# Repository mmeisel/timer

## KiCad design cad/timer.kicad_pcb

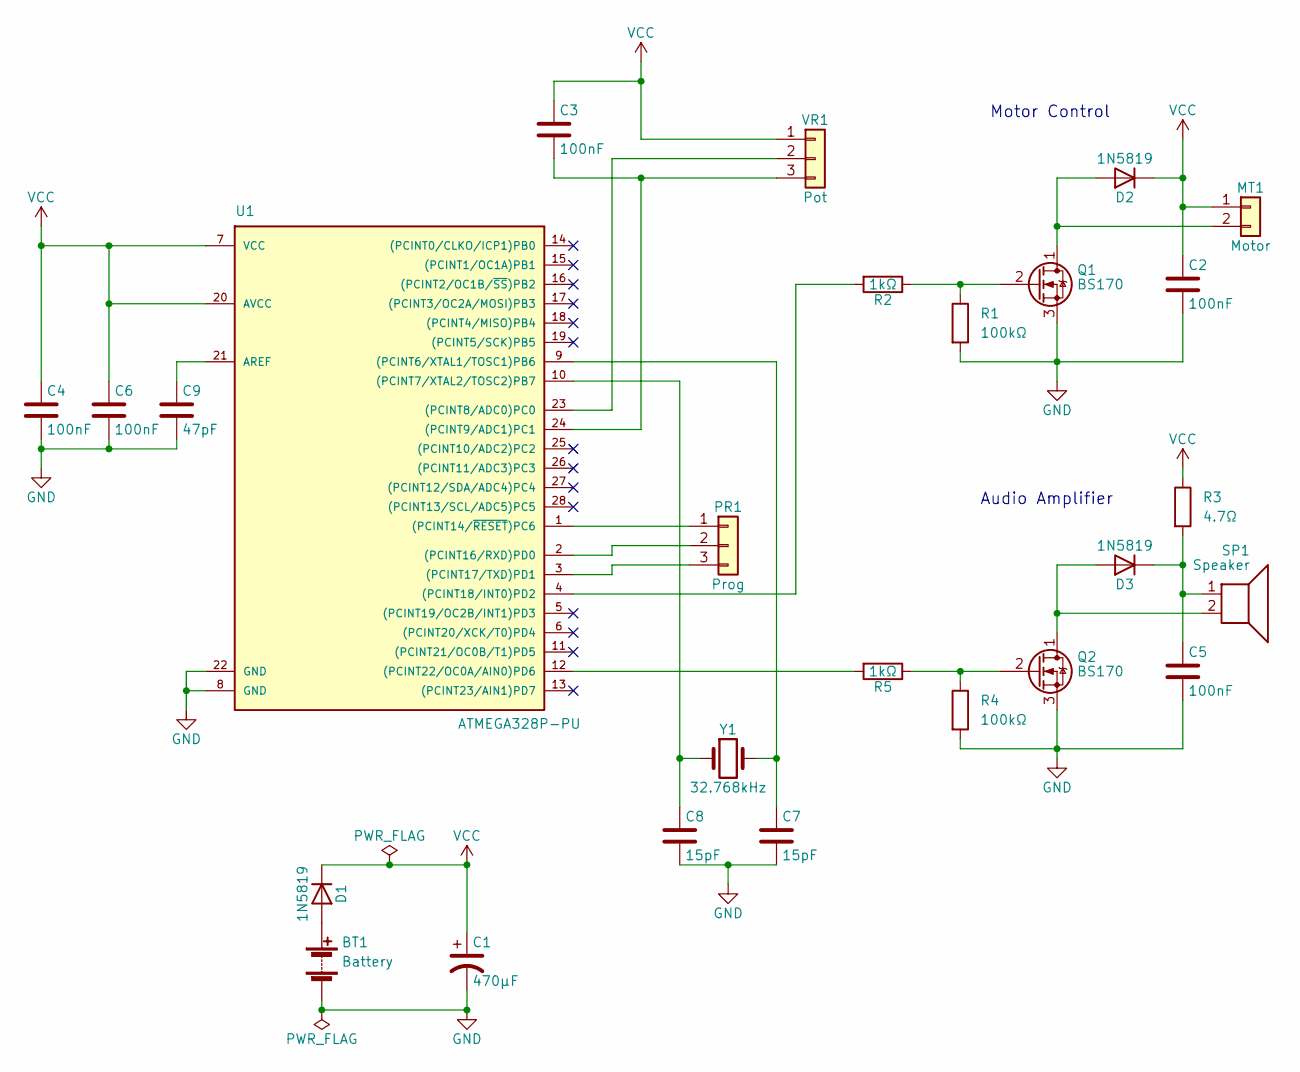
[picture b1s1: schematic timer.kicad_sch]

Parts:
BT1: Battery; PinHeader_1x02_P2.54mm_Vertical
C1: 470µF; CP_Radial_D10.0mm_P5.00mm
C2, C3, C4, C5, C6: 100nF; C_Disc_D5.0mm_W2.5mm_P5.00mm
C7, C8: 15pF; C_Disc_D5.0mm_W2.5mm_P2.50mm
C9: 47pF; C_Disc_D5.0mm_W2.5mm_P2.50mm
D1, D2, D3: 1N5819; D_DO-41_SOD81_P2.54mm_Vertical_KathodeUp
MT1: Motor; PinHeader_1x02_P2.54mm_Vertical
PR1: Prog; PinHeader_1x03_P2.54mm_Vertical
Q1, Q2: BS170; TO-92_Inline_Wide
R1, R4: 100kΩ; R_Axial_DIN0207_L6.3mm_D2.5mm_P2.54mm_Vertical
R2, R5: 1kΩ; R_Axial_DIN0207_L6.3mm_D2.5mm_P2.54mm_Vertical
R3: 4.7Ω; R_Axial_DIN0207_L6.3mm_D2.5mm_P2.54mm_Vertical
SP1: Speaker; PinHeader_1x02_P2.54mm_Vertical
U1: ATMEGA328P-PU; DIP-28_W7.62mm_Socket
VR1: Pot; PinHeader_1x03_P2.54mm_Vertical
Y1: 32.768kHz; Crystal_C38-LF_D3.0mm_L8.0mm_Vertical

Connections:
GND: BT1.2 (-), C1.2, C2.2, C4.2, C5.2, C6.2, C7.2, C8.2, C9.2, Q1.3 (S), Q2.3 (S), R1.2, R4.2, U1.8 (GND), U1.22 (GND)
unnamed: BT1.1 (+), D1.2 (A)
unnamed: C3.2, U1.24 ((PCINT9/ADC1)PC1), VR1.3
unnamed: C5.1, D3.1 (K), R3.2, SP1.1
unnamed: C7.1, U1.9 ((PCINT6/XTAL1/TOSC1)PB6), Y1.2
unnamed: C8.1, U1.10 ((PCINT7/XTAL2/TOSC2)PB7), Y1.1
unnamed: C9.1, U1.21 (AREF)
unnamed: D2.2 (A), MT1.2, Q1.1 (D)
unnamed: D3.2 (A), Q2.1 (D), SP1.2
unnamed: PR1.1, U1.1 ((PCINT14/~RESET)PC6)
unnamed: PR1.2, U1.2 ((PCINT16/RXD)PD0)
unnamed: PR1.3, U1.3 ((PCINT17/TXD)PD1)
unnamed: Q1.2 (G), R1.1, R2.1
unnamed: Q2.2 (G), R4.1, R5.1
unnamed: R2.2, U1.4 ((PCINT18/INT0)PD2)
unnamed: R5.2, U1.12 ((PCINT22/OC0A/AIN0)PD6)
unnamed: U1.23 ((PCINT8/ADC0)PC0), VR1.2
VCC: C1.1, C2.1, C3.1, C4.1, C6.1, D1.1 (K), D2.1 (K), MT1.1, R3.1, U1.7 (VCC), U1.20 (AVCC), VR1.1

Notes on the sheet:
Audio Amplifier
Motor Control

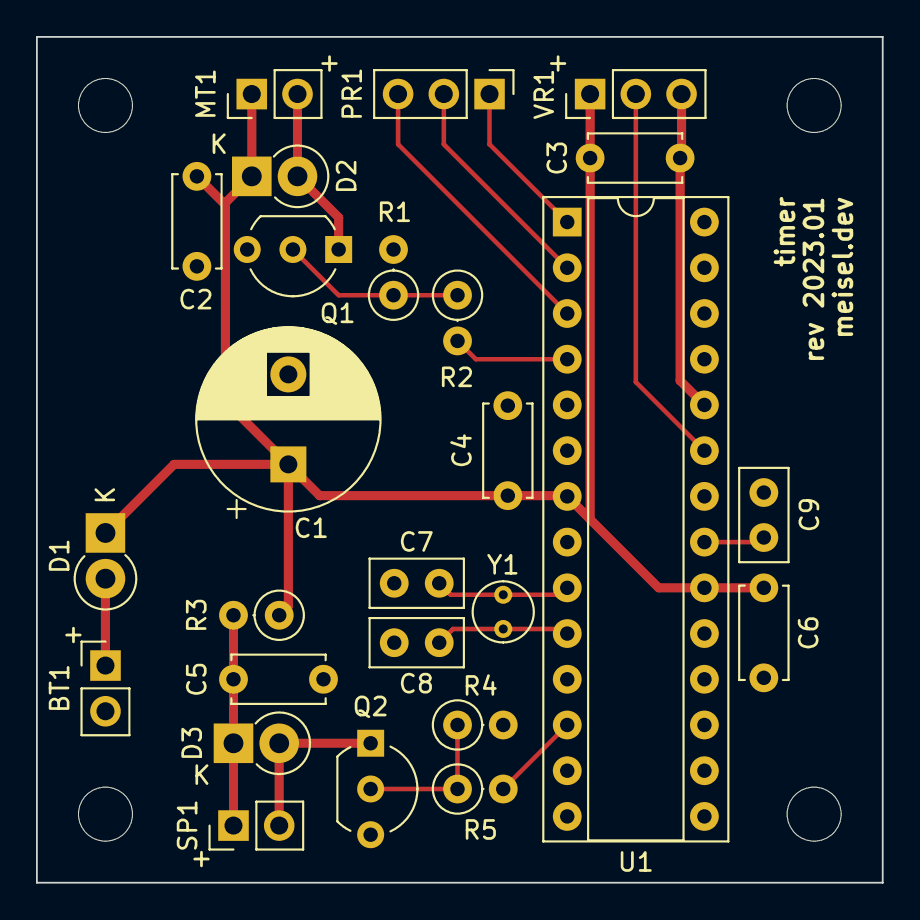
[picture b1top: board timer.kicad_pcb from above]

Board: 2 copper layers, 47.0 x 47.0 mm, 30 parts (0 on the bottom side), 18 nets.

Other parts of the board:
H1, H2, H3, H4: MountingHole_3mm

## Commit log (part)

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2017-07-17 First attempt
    - Using PID to set slider position (untested)
    - Working feedback mechanism with linear scale
2017-07-18 Mostly failed attempt to work with H-Bridge
2017-07-18 Not working version with PID
2017-07-18 Mostly working 30-second linear version
2017-07-19 Reliability and efficiency improvements
2017-07-19 Use binary search in stopBefore
2017-07-19 Tweak some comments
2017-07-19 Fix detentes and improve change detection
2017-07-20 New detentes (non-linear scale)
2017-08-06 Add interrupt for external slide detection circuit
    This doesn't actually do much yet since the microprocessor only sleeps
    for at most 1 ms until the next interrupt for millis(), and it's using
    the highest power sleep mode (idle).
    This will actually start to be useful when using a crystal for the clock
    instead of the Arduino library's (interrupt-based) millis().
2017-08-06 Add notes to version control
2017-08-06 Simpler interrupt handling
2017-08-06 Ignore .DS_Store files
2017-08-06 Initial attempt at interrupt-based timing
2017-08-06 Some code cleanup
2017-08-07 Mostly working low power version!
2017-08-07 Better serial output for debugging
2017-08-08 Some important tweaks for correct operation
2017-08-08 Safer handling of secondsRemaining_
2017-08-08 Don't wake up at all in the OFF position
2017-08-08 TODOs and comments
2017-08-08 Try getting rid of DIR_STOP, doesn't seem to do much
2017-08-08 Use fast stop for longer to see if that stops chatter
2017-08-09 Some notes
2017-08-10 First attempt at new scheme
2017-08-11 Big rewrite
    - Much simpler and more efficient loop() function
    - Sleep a lot more
    - No more detentes for now :(
    - Code cleanup
    - Generate stops of equal size
    - More details in notes.txt
2017-08-14 Fix timing issues by waiting for crystal to stabilize
2017-08-14 Better Timer2 register handling
2017-08-14 Improvements and bug fixes
    - Generate stops on startup instead of on demand
    - Better debug messages
    - Fix tick bug
    - Don't allow the motor to be interrupted
2017-08-24 Some cleanup, tweaks, and notes
    Including:
    - Remove redundant call to updateBell()
    - Better name for power on/off interrupt pin
2017-08-28 Wait for crystal to stabilize by comparing with millis()
2017-09-01 PCM: Use Timer0 instead of Timer2
2017-09-01 Store stops in flash
2017-09-01 Prep for audio generation
    - Add the PCM library from https://github.com/damellis/PCM directly in
    the project (it will need some modifications)
    - Change output pins for compatibility with PCM
    - Some notes on the subject
2017-09-04 Rename stopwatch to clock
2017-09-04 Add source audio file and edited version
2017-09-04 First attempt at complete PCM-based bell
2017-09-14 PCM: More reliable and faster isPlaying() check
2017-09-14 Initialize speaker pin to low
    Otherwise, it wastes power.
2017-09-14 Less lenient position change detection
2017-09-14 Some TODOs
2017-09-14 Fixes for sound generation
    - Don't do anything else while a sound is playing
    - Wait until the motor is done moving the slider into position before
    trying to generate audio
2017-09-15 Remove unnecessary call to updateMotor() on setup()
    We just set the position so there can never be anything to do at
    this point.
2017-09-15 Notes on Class B amplifier circuit
2017-09-15 Remove use of millis() in debug output
    This is already pretty useless and will soon be disabled.
2017-09-15 PCM: Just disable Timer0 instead of restoring it
    Partially reverts 548f2e9945915deeff77d4df83d5430c6061481a
2017-09-15 Fix stopwatch overflow bug
    The subtraction needs to be cast to a signed integer with the same
    number of bits, or the trick doesn't work.
2017-09-15 Use Timer0 directly for stabilization
    This is more accurate than using millis().
2017-09-15 Expose current clock time
2017-09-15 Improve adc reliability
    - Don't try to start two conversions at once
    - Use idle instead of ADC noise reduction low-power mode to avoid
    interfering with Timer2
2017-09-15 Alternative bell sound
    (But I don't like it as much.)
2017-09-15 Play the bell a little less frequently
2017-09-15 Add a TODO
2017-09-15 Switch motor driver on/off with transistor
2017-09-16 Don't set OCR0A initially
    This seems to do nothing other than cause an audible pop.
2017-09-18 bell2 fixup
2017-09-18 Add schematic and unfinished PCB
2017-09-20 Through-hole parts are on front AND back!
2017-09-20 Actual stops for production
2017-09-20 Larger off stop
    No need for zero to be bigger than the other stops, better to have a
    little extra space for the off position. The soft power switch will need
    to have its resistor adjusted accordingly.
2017-09-20 CAD changes for off stop size change
    The soft power switch needs a 68k instead of a 47k resistor now.
2017-10-17 Fix outdated motor-related comment, add note
2017-10-18 Front panel in Front Panel Designer format
    This is the software from Front Panel Express.
2017-10-18 Exported front panel in DXF format
2017-11-08 PCB: Q2 and Q3 labels were switched!
2017-11-30 Fewer stops (39 instead of 60)
2017-11-30 Basic version of 3D-modeled front panel
    Using OpenSCAD
2017-11-30 Clean up front panel slightly
2017-11-30 SCAD code cleanup (fewer braces)
2017-11-30 Front panel: added detentes
2017-11-30 Front panel: fancier off markings
    The same halftone dots as in the Front Panel Designer version
2017-11-30 Front panel: Alternate OFF markings
    With the "OFF" label
2017-11-30 Front panel: Make panel depth adjustable
2017-11-30 Front panel: Deeper engravings
2017-12-02 New 2D version of front panel
    This one is for laser cutting
2017-12-05 2D front panel: More overlap with knob
2017-12-05 Stop at the middle of the stop, not the beginning
2017-12-05 SIGNIFICANT_POSITION_CHANGE is no longer needed
    Using the middle of the stop as the target makes a false detection of
    movement much less likely, so this shouldn't be necessary.
2017-12-05 Front panel: Add SVG for Ponoko
    This had to be customized by hand to meet their design guidelines.
2017-12-07 Front panel: Spread OFF marks to match longer lines
2017-12-10 Updated front panel SVG with recent changes
2017-12-10 Further progress on enclosure for 3D printing
    However, I'm giving up on this approach in favor of laser cutting.
2017-12-12 Start of 2D enclosure for laser cutting
    Still very much WIP. First version of top and back panels.
2017-12-14 More progress on new enclosure
    Still to do:
    - Fix kerf issues
    - Add front panel
    - Add interior panel
    - Add something to mount the battery
2017-12-14 Fixed some kerf issues with 2D enclosure
2017-12-14 Added all panels, still some TODOs
2017-12-15 Fit both batteries and PCB on bottom
2017-12-17 Add screw holes to front panel
2017-12-17 Add correct measurements for slider hole
2017-12-17 Line all parts up
    Two sets will fit on one Ponoko P2 panel this way!
2017-12-17 SVG files for Ponoko laser cut order
    Sent to Ponoko for first run
2017-12-21 Add missing $fn for some screw holes
2017-12-22 Tweak hinge hole position so back panel is flush
2017-12-27 Front panel: Remove corner screw holes
    No need for the holes, I can just glue it
2017-12-27 Front panel: Fix inaccuracy due to slider properties
    According to the datasheet, the slider potentiometer output voltage
    doesn't change for the first or last 2 (+- 1) mm of travel. So spead the
    markings across 96mm instead of 100mm.
2017-12-27 Front panel: More visible off markings
2017-12-27 Front panel: Some tweaks for next run
    - I'm giving up on the tactile feedback for now, so reduce the overlap
    between the knob and the lines
    - Make the lines thinner (they'll just be engraved now)
    - Shrink the width of the slider opening so it stops when it hits the
    plastic instead of at its ultimate limit
2017-12-27 Front panel: New files for next Ponoko order
2017-12-30 More reliable motor controller switch
    The previous resistor/transistor combo wasn't reliable
2017-12-30 Reposition the slider to the center of the stop
    After someone sets the stop manually, move the slider to the center of
    the stop. This serves two purposes:
    - It prevents the timer from getting stuck between two stops when
    positioned at a stop boundary
    - It gives the user some feedback as to which stop was selected
2018-01-07 Remove unused motor function
2018-01-07 Updated schematic and PCB design
    - Increased hole size to 3mm
    - Removed motor controller on/off switch (Q1 and R3)
    - Swap transistor footprint for one that's easier to solder
    - Reroute with FreeRoutingNew
2018-01-10 Refactor for reverse-only motor control
    The L293D has too big a voltage drop to run the already undervolted
    motor on the slider. It both drops Vcc and raises ground due to the
    transistors in the H-bridge.
2018-01-11 Remove extraneous setting of ouptut mode on PCM pin
2018-01-11 Reduce clicks when bell sound starts
    No more clicks! Just needed to ramp up from zero.
2018-01-12 Schematic for updated design
    - Now using MOSFETs for both motor and audio switching
    - Added a bunch of bypass/decoupling capacitors
2018-01-12 New PCB design to match new schematic
    - Isolated power networks with decoupling capacitors
    - Top layer is ground, bottom layer is VCC (this seems to be the
    convention)
    - Hopefully better placement of ports for external devices
2018-01-16 Enclosure: Add some wiggle room for door
2018-01-18 Just some thoughts
2018-01-20 One more note
2018-01-20 New ringing behavior
    - The timer will now only ring a set number of times, then turn itself
    off. This way it won't just keep ringing until it drains the battery
    if it's left ringing unattended.
    - Allow the delay to be variable between rings by providing an array of
    delay intervals.
2018-02-09 Less aggressive bell repetition
2018-02-09 Some notes on battery holders and enclosure
2018-03-28 Add note about "click" branch
2018-03-28 New battery holder
2018-03-28 Fix tilt angle, bottom depth, and clean up code
2018-03-28 Rearrange parts to fit better in ponoko template
2018-03-28 I only need one of these!
2018-03-28 Avoid rounded edges when using offset()
2018-03-28 Add some padding to battery rail cutouts
    For some reason the rendering of these was imprecise.
2018-03-28 Update enclosure SVG files
    Note that the battery crossbar was manually combined with the slider
    cutout using inkscape.
2018-08-21 Enclosure tweaks
    - Remove battery crossbar
    - Slightly more room for battery holder
    - Move PCB mount a bit closer to the rear door
2021-10-12 Prevent warning on newer OpenSCAD
2021-10-15 Add licenses
2021-10-15 First attempt at click sound
2021-10-22 Changes from new kicad version
2022-01-05 Fix some comments
2022-10-10 Remove unused parameter
2022-10-10 Naming tweak for MiniCore compatibility
2022-10-10 Better config/debug system
    No functional changes
2022-10-10 Some additional notes
2023-01-05 Remove comparator, big logic cleanup
2023-01-05 Don't enter ADC noise reduction mode too quickly
2023-01-09 Reset bell parameters any time stop zero is hit
2023-01-17 Give feedback when timer is set
    - Feedback is by playing the second half of the bell sound, which
    sounds like a quieter ring of the bell
    - Also improve debug logging and config system
2023-01-20 Take most precise possible ADC measurements
2023-01-21 Change pin to accomodate PCB layout
2023-01-21 Update CAD for redesign
    Also cleanup old files in cad directory
2023-01-21 Label PCB
2023-01-24 Add markers for positive terminals
2023-01-24 Prevent false human detection when motor is running
2023-01-24 Missed one positive terminal marker
